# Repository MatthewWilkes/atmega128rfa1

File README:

This is open source hardware, licensed under the CERN open hardware licence.

This is a development board for the ATMega128rfa1 with optional USB interface.

It is intended to be a minimal viable board for low power applications, hence the low level of LEDs.  Programming of the chip can be done with minimal components installed (just the decoupling capacitor is required), but viable RF is expected to take a lot more.

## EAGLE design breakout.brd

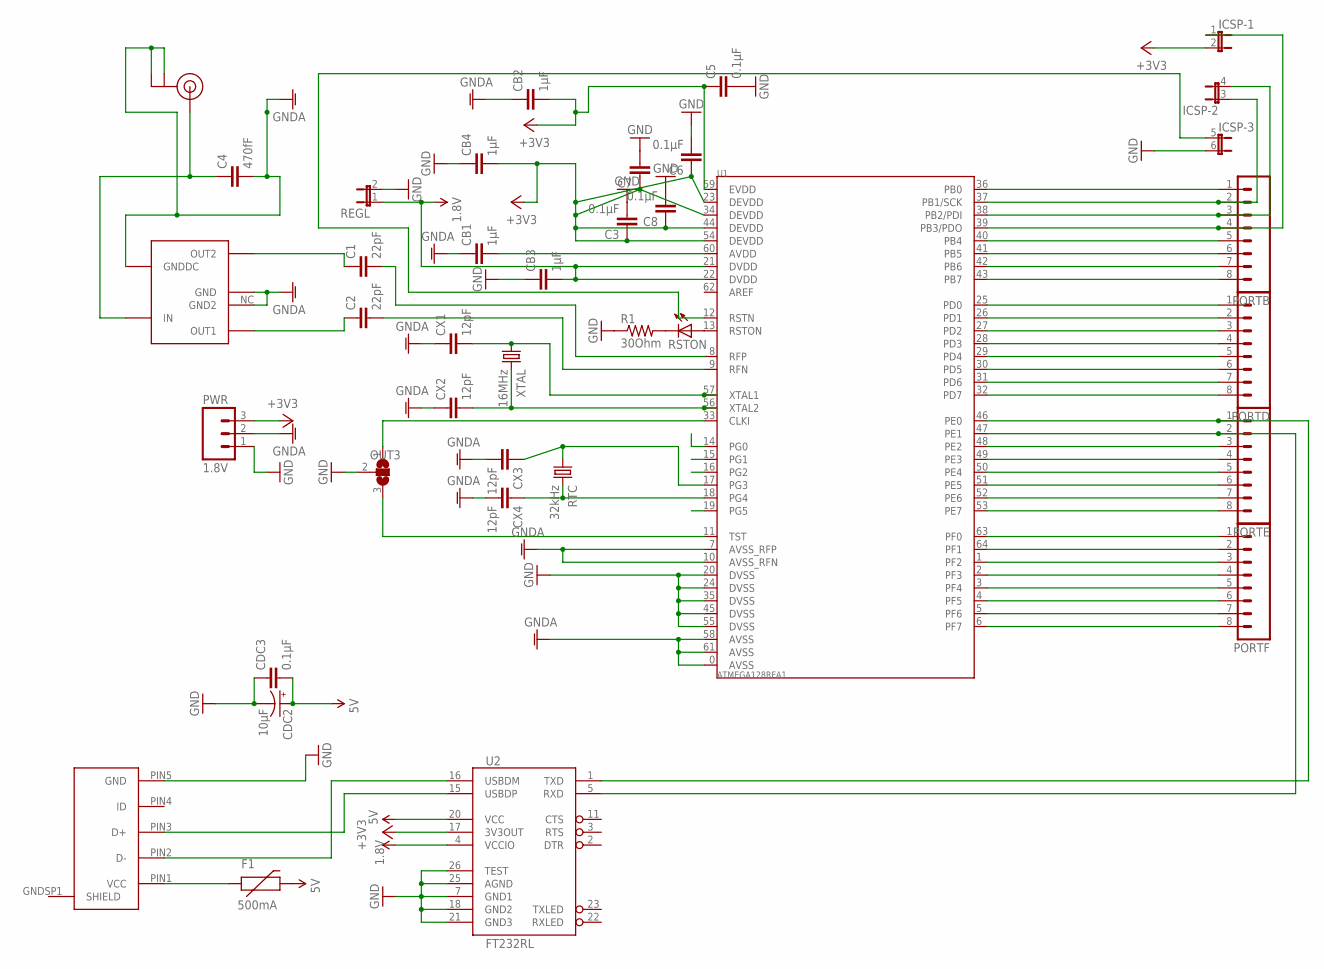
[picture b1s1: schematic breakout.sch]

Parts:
B1: 2.4GHz; WE-BAL
C1, C2: 22pF; C0603
C3, C5, C6, C8: 0.1µF; C0201
C4: 470fF; C0402
C7: C-EUC0201; C0201
CB1, CB2, CB3, CB4: 1µF; C0603
CDC2: 10µF; EIA3216
CDC3: 0.1µF; C0201
CX1, CX2, CX3, CX4: 12pF; C0603
F1: 500mA; 0603
ICSP: JP3QE; JP3Q
JP1: USBMICROB; MICROB
OUT3: SOLDERJUMPERNO; SJ_2
PORTB: M081X08; 1X08
PORTD: M081X08; 1X08
PORTE: M081X08; 1X08
PORTF: M081X08; 1X08
PWR: 1.8V; 1X03
R1: 30Ohm; R0603
REGL: JP1E; JP1
RSTON: LEDCHIPLED_0603; CHIPLED_0603
RTC: 32kHz; TC26H
U1: ATMEGA128RFA1; QFN-64
U2: FT232RL; SSOP28DB
U$6: U.FL
XTAL: 16MHz; HC49UP

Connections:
1.8V: CB3.2, REGL.1, U1.21 (DVDD), U1.22 (DVDD), U2.4 (VCCIO)
5V: CDC2.A (+), CDC3.2, F1.2, U2.20 (VCC)
+3V3: C3.1, C5.1, C6.1, C7.1, C8.1, CB2.2, CB4.2, ICSP.2, PWR.3, U1.23 (DEVDD), U1.34 (DEVDD), U1.44 (DEVDD), U1.54 (DEVDD), U1.59 (EVDD), U2.17 (3V3OUT)
GND: C3.2, C5.2, C6.2, C7.2, C8.2, CB3.1, CB4.1, CDC2.C (-), CDC3.1, ICSP.6 (2), JP1.PIN5 (GND), OUT3.2, PWR.1, R1.1, REGL.2, U1.20 (DVSS), U1.24 (DVSS), U1.35 (DVSS), U1.45 (DVSS), U1.55 (DVSS), U2.7 (GND1), U2.18 (GND2), U2.21 (GND3), U2.25 (AGND), U2.26 (TEST)
GNDA: B1.GND, B1.GNDDC, B1.NC (GND2), C4.2, CB1.1, CB2.1, CX1.1, CX2.1, CX3.2, CX4.2, PWR.2, U1.0 (AVSS), U1.7 (AVSS_RFP), U1.10 (AVSS_RFN), U1.58 (AVSS), U1.61 (AVSS), U$6.P$1 (GND), U$6.P$2 (GND)
unnamed: CX3.1, RTC.1, U1.17 (PG3)
unnamed: CX4.1, RTC.2, U1.18 (PG4)
unnamed: ICSP.1, PORTB.4, U1.39 (PB3/PDO)
unnamed: CB1.2, U1.60 (AVDD)
unnamed: B1.OUT1, C2.1
unnamed: ICSP.3 (1), PORTB.2, U1.37 (PB1/SCK)
unnamed: OUT3.1, U1.33 (CLKI)
unnamed: PORTD.1, U1.25 (PD0)
unnamed: C2.2, U1.9 (RFN)
unnamed: CX2.2, U1.56 (XTAL2), XTAL.2
unnamed: PORTD.2, U1.26 (PD1)
unnamed: ICSP.5 (1), U1.12 (RSTN)
unnamed: CX1.2, U1.57 (XTAL1), XTAL.1
unnamed: C1.2, U1.8 (RFP)
unnamed: B1.OUT2, C1.1
unnamed: PORTD.3, U1.27 (PD2)
unnamed: PORTD.4, U1.28 (PD3)
unnamed: JP1.PIN3 (D+), U2.15 (USBDP)
unnamed: PORTD.5, U1.29 (PD4)
unnamed: PORTD.6, U1.30 (PD5)
unnamed: PORTD.7, U1.31 (PD6)
unnamed: PORTD.8, U1.32 (PD7)
unnamed: PORTE.1, U1.46 (PE0), U2.1 (TXD)
unnamed: PORTE.2, U1.47 (PE1), U2.5 (RXD)
unnamed: PORTE.3, U1.48 (PE2)
unnamed: PORTE.4, U1.49 (PE3)
unnamed: PORTE.5, U1.50 (PE4)
unnamed: PORTE.6, U1.51 (PE5)
unnamed: PORTE.7, U1.52 (PE6)
unnamed: PORTE.8, U1.53 (PE7)
unnamed: PORTF.1, U1.63 (PF0)
unnamed: PORTF.2, U1.64 (PF1)
unnamed: PORTF.3, U1.1 (PF2)
unnamed: PORTF.4, U1.2 (PF3)
unnamed: PORTB.1, U1.36 (PB0)
unnamed: PORTB.5, U1.40 (PB4)
unnamed: PORTB.6, U1.41 (PB5)
unnamed: PORTB.7, U1.42 (PB6)
unnamed: PORTB.8, U1.43 (PB7)
unnamed: OUT3.3, U1.11 (TST)
unnamed: JP1.PIN2 (D-), U2.16 (USBDM)
unnamed: F1.1, JP1.PIN1 (VCC)
unnamed: RSTON.A, U1.13 (RSTON)
unnamed: R1.2, RSTON.C
unnamed: ICSP.4 (2), PORTB.3, U1.38 (PB2/PDI)
SMA: B1.IN, C4.1, U$6.P$3 (SIGNAL)
TCK: PORTF.5, U1.3 (PF4)
TDI: PORTF.8, U1.6 (PF7)
TDO: PORTF.7, U1.5 (PF6)
TMS: PORTF.6, U1.4 (PF5)

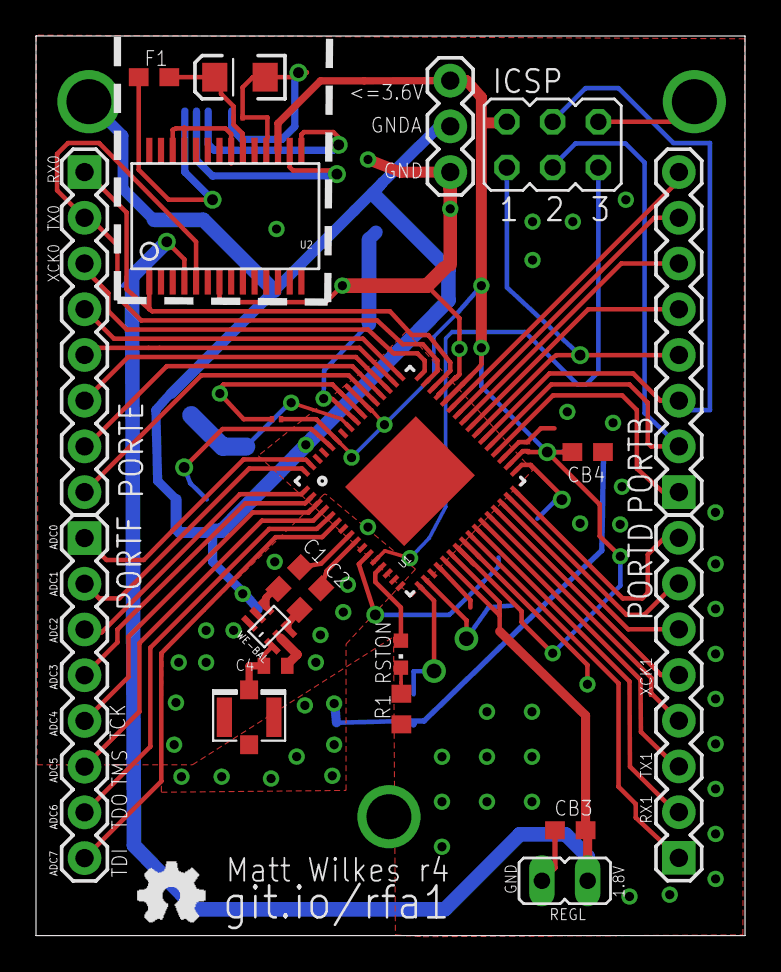
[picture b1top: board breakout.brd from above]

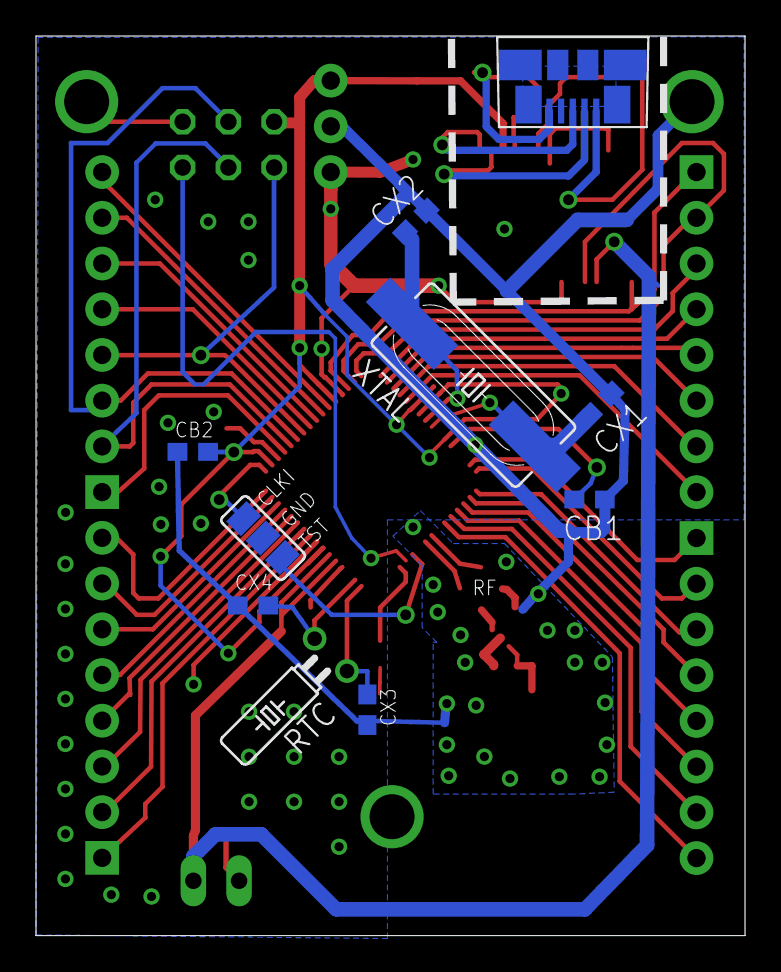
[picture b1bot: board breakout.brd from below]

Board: 2 copper layers, 39.4 x 50.0 mm, 36 parts (10 on the bottom side), 55 nets.

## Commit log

2012-03-30 initial
2012-03-30 Current status
2012-03-30 Remove preferences
2012-04-01 Better routing of source voltages.
2012-04-01 DRC fixes
2012-04-01 Fix airwires, albeit with suboptimal RF and analog ground connection. Maybe we need some chokes.
2012-04-01 Add +1V8 copper fill
2012-04-01 Use GNDDC from the balun for the SMA antenna ground
2012-04-01 DRC fix
2012-04-01 More attempts at an RF plane
2012-04-01 Groundings
2012-04-08 misc uncommitted updates
2012-04-08 Schematic USB support
2012-04-08 Normalise some packages, the caps we have are 0603 not 0504, whatever that is.
2012-04-08 Tidy
2012-04-08 License under CERN OHL
2012-04-08 Readme
2012-04-08 Remove 3.3V rail between USB and regulator, it can only source 50mA. DRC fixes. Make bottom copper fill 1.8V regl output.
2012-04-08 Add second copper pour to bottom layer to isolate RF circuitry
2012-04-08 Move usb closer to the new edge
2012-04-08 USB silkscreen
2012-04-09 Tie test low
2012-04-09 Remove un-needed 1.8V wire as the bottom plane handles it now
2012-04-09 Silkscreening for JTAG
2012-04-09 Reattach 3.3V, it can source 50mA and the 128rfa1 at full power TX only needs 20ish.
2012-04-09 Routing perfectionism
2012-04-12 Created gh-pages branch via GitHub
2012-04-27 Bind grounds with tented vias, some rerouting
2012-04-27 Impedence matching
2012-04-27 Silkscreen
2012-04-27 Silkscreens and fiddling
2012-04-27 Move GNDA bottom plane to avoid a top layer digital line
2012-04-27 Ground coupling tented via underneath the atmega
2012-04-27 Switch CLKI/TST jumper with a 3way including a central GND
2012-04-27 Widen some ground traces
2012-04-27 Ensure GPIO is on a .1" grid vertically
2012-04-27 Ensure GPIO is on a .1" grid horizontally
2012-04-27 Remove some ugly vias
2012-04-27 Move a via into the GND layer
2012-04-27 Dodge power out of the way of a silkscreen line
2012-04-27 Move PORTE silkscreen to be clearer
2012-05-09 Multiple fixes to decoupling, board layouts, this is okay
2012-05-09 Thicken up +3V3 rail
2012-05-09 Erc errors
2012-05-09 Realign power and improve overall silking. Switched to Vector font
2012-05-09 Persist font vectoring
2012-05-09 Layout tweaks
2012-05-09 Dewonky some of PORTE
2012-05-09 Route nicifying
2012-05-09 Line straightening
2012-05-09 Route prettifying
2012-05-09 Cleanup ground pours to give some more room around the RF ground, fix airwires
2012-05-09 Additional GND bridging via
2012-05-10 Remove silking for 0.1µF cap
2012-05-10 Layout tidying
2012-05-10 Align power to 0.1 inch horiz
2012-05-21 Various fixes, r3 ordered
2012-06-08 Various r4 changes
2012-06-08 Add image of r3 boards
2012-06-08 Link image
2012-09-12 Switch to XML based representation
2012-12-30 Switch to using a u.fl connector from SMA
2012-12-30 Reduce the size of the radio copper pour to fit u.fl
2012-12-30 Bump revision number

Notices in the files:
parts and their libraries:
SparkFun-Connectors: Licensing: CC v3.0 Share-Alike You are welcome to use this library for commercial purposes.
